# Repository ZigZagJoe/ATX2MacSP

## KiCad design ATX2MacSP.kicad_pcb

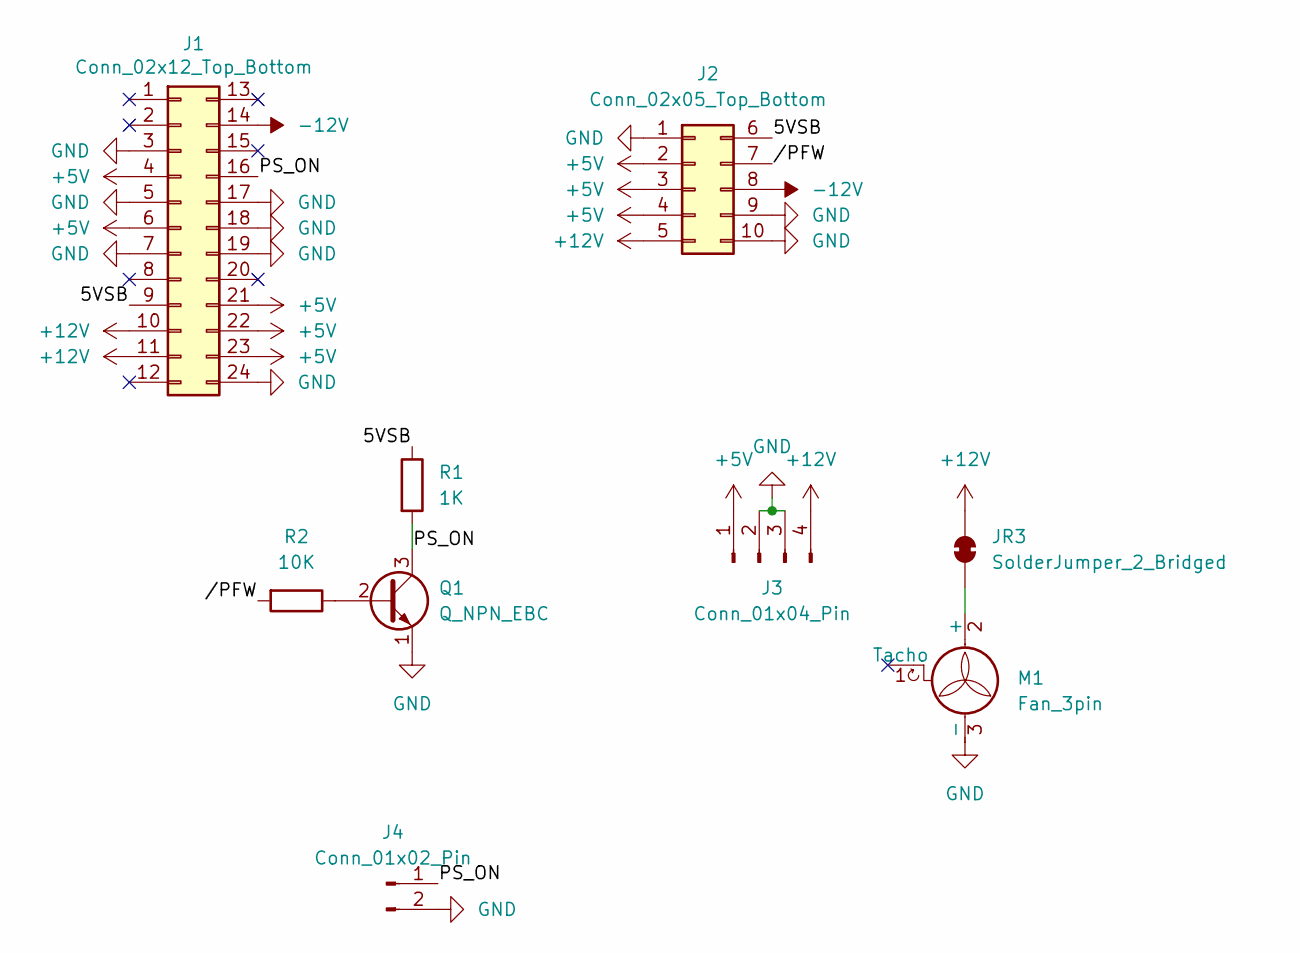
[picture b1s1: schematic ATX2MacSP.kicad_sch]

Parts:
J1: Conn_02x12_Top_Bottom; Molex_Mini-Fit_Jr_5566-24A_2x12_P4.20mm_Vertical
J2: Conn_02x05_Top_Bottom; Molex_Mini-Fit_Jr_5566-10A2_2x05_P4.20mm_Vertical
J3: Conn_01x04_Pin; Samtec_HPM-04-05-x-S_Straight_1x04_Pitch5.08mm
J4: Conn_01x02_Pin; PinHeader_1x02_P2.54mm_Vertical
JR3: SolderJumper_2_Bridged; SolderJumper-2 Bridged Resistor THT
M1: Fan_3pin; FanPinHeader_1x03_P2.54mm_Vertical
Q1: Q_NPN_EBC; TO-92L_Inline_Wide
R1: 1K; R_Axial_DIN0204_L3.6mm_D1.6mm_P7.62mm_Horizontal
R2: 10K; R_Axial_DIN0204_L3.6mm_D1.6mm_P7.62mm_Horizontal

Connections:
+5V: J1.4, J1.6, J1.21, J1.22, J1.23, J2.2, J2.3, J2.4, J3.1
+12V: J1.10, J1.11, J2.5, J3.4, JR3.2 (B)
-12V: J1.14, J2.8
/5VSB: J1.9, J2.6, R1.1
/PS_ON: J1.16, J4.1, Q1.3 (C), R1.2
//PFW: J2.7, R2.2
GND: J1.3, J1.5, J1.7, J1.17, J1.18, J1.19, J1.24, J2.1, J2.9, J2.10, J3.2, J3.3, J4.2, M1.3 (-), Q1.1 (E)
unnamed: JR3.1 (A), M1.2 (+)
unnamed: Q1.2 (B), R2.1

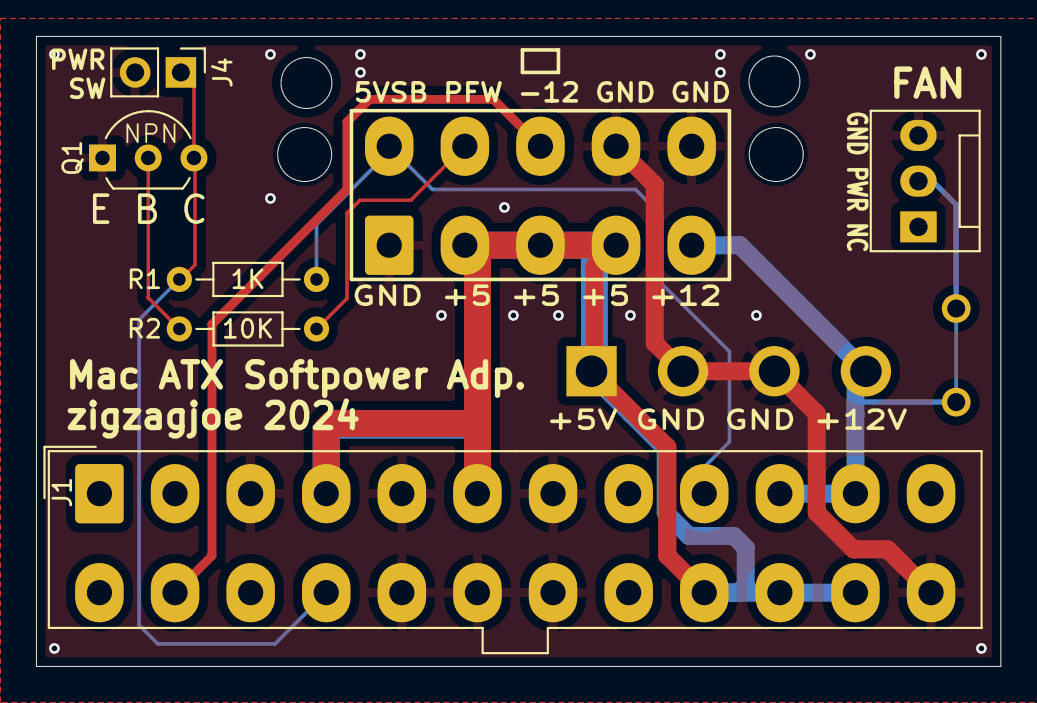
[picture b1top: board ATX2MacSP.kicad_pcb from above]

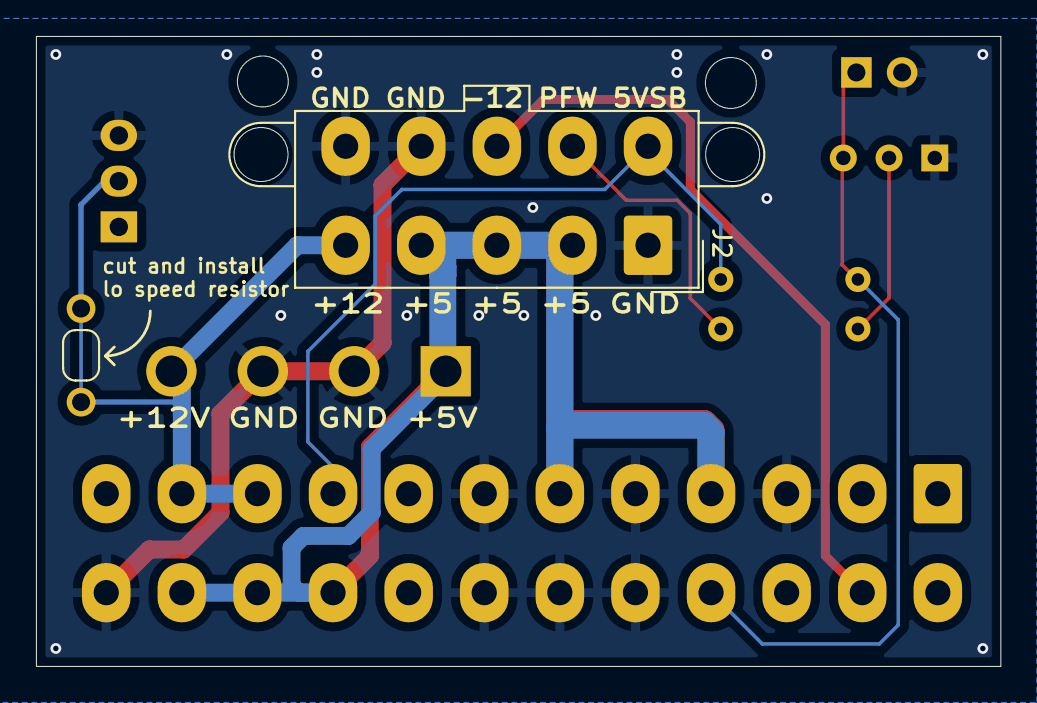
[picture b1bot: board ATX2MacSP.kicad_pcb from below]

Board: 2 copper layers, 53.6 x 35.0 mm, 9 parts (2 on the bottom side), 9 nets.

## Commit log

2024-09-19 add pcb image and readme
